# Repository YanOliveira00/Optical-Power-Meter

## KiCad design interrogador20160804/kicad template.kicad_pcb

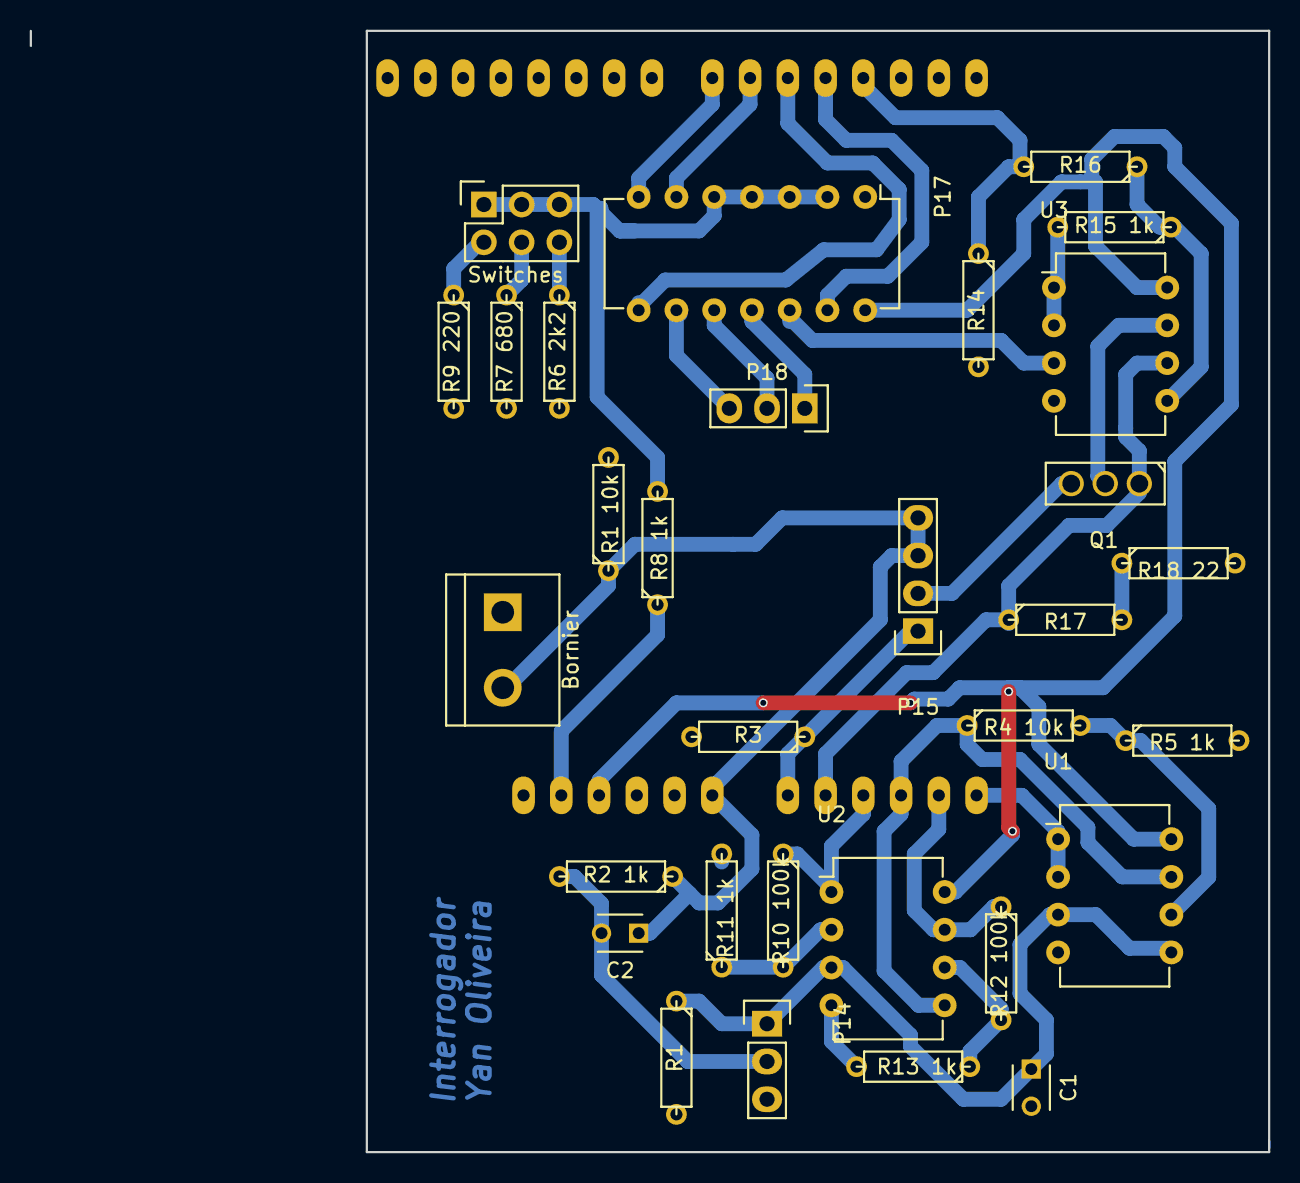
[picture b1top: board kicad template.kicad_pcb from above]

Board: 2 copper layers, 83.3 x 75.4 mm, 32 parts (1 on the bottom side), 33 nets.

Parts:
Bornier: PowerIn; bornier2
C1: 100p; C_Disc_D3_P2.5
C2: 100n; C_Disc_D3_P2.5
P14: Detector; Socket_Strip_Straight_1x03
P15: laser (PD+LD); Pin_Header_Straight_1x04
P17: TLC5620; DIP-14_W7.62mm
P18: extout; Socket_Strip_Straight_1x03
Q1: Q_NPN_EBC; SOT126_SOT32_Housing_Vertical
R1, R1 10k, R3, R4 10k: 10k; R3
R2 1k, R5 1k, R8 1k, R11 1k, R13 1k, R15 1k: 1k; R3
R6 2k2: 2k2; R3
R7 680: 680; R3
R9 220: 220; R3
R10 100k, R12 100k, R14: 100k; R3
R16: 15k; R3
R17: 10; R3
R18 22: 22; R3
SHIELD1: ARDUINO_SHIELD
Switches: CONN_02X03; Socket_Strip_Straight_2x03
U1, U2, U3: MCP6002; DIP-8_W7.62mm

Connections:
+3V3: R8 1k.1, SHIELD1.3V3
+5V: P17.14, SHIELD1.5V, U1.8, U2.8, U3.8
/1X: SHIELD1.AD5, U1.1, U1.2
/10X: R4 10k.1, SHIELD1.AD3, U1.7, U2.5
/100X: R10 100k.1, SHIELD1.AD2, U2.1
/1000X: R12 100k.1, SHIELD1.AD4, U2.7
/AMPFEED: Q1.1, R17.1, SHIELD1.AD1, U3.6
/CLK: P17.7, SHIELD1.7
/DAC_A: R15 1k.2, U3.1, U3.2
/DATA: P17.6, SHIELD1.6
/LD: P15.2, Q1.3
/LDAC: P17.13, SHIELD1.4
/LOAD: P17.8, SHIELD1.5
/MOD: R14.1, R16.2, SHIELD1.3
/PD: P15.1, R3.1, SHIELD1.AD0
/input: C1.1, P14.1, R1.1, U1.3, U1.5, U2.3
GND: Bornier.1, C1.2, P14.3, P17.1, R1.2, R1 10k.2, R3.2, R5 1k.2, R6 2k2.2, R7 680.2, R9 220.2, R11 1k.2, R13 1k.2, R14.2, R18 22.2, SHIELD1.GND1, SHIELD1.GND2, SHIELD1.GND3, U1.4, U2.4, U3.4
unnamed: C2.2, P14.2, R2 1k.2
unnamed: P17.2, P17.3, P17.4, P17.5, R8 1k.2, Switches.1, Switches.3, Switches.5
unnamed: R9 220.1, Switches.2
unnamed: R7 680.1, Switches.4
unnamed: R6 2k2.1, Switches.6
unnamed: P17.9, P18.3
unnamed: P17.10, P18.2
unnamed: P17.11, P18.1
unnamed: P17.12, U3.3
unnamed: Q1.2, U3.7
unnamed: R4 10k.2, R5 1k.1, U1.6
unnamed: R10 100k.2, R11 1k.1, U2.2
unnamed: R12 100k.2, R13 1k.1, U2.6
unnamed: R15 1k.1, R16.1, U3.5
unnamed: R17.2, R18 22.1
VCC: Bornier.2, C2.1, P15.3, P15.4, R1 10k.1, R2 1k.1, SHIELD1.V_IN

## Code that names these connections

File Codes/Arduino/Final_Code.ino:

//Código criado por Yan S. de Oliveira, em 2016.
//Código complementar feitos em Python.
//Corresponde ao TCC do curso de Engenharia da Computação UFPa.
//Editado e comentado em 17/03/2017 
//Definições iniciais
//Pinos do TLC5620 6,7,8 e 13, respectivamente.
#define PIN_DATA  6  
#define PIN_CLK   7  
#define PIN_LOAD  5  
#define PIN_LDAC  4  
#define PIN_MOD  3 //Trabalhos futuros 

//Portas que serão utilizadas para a placa e seus feedbacks
#define PIN_AMPFEED  A1
#define PIN_PDFEED A0
#define PIN_1X A5
#define PIN_100X A2
#define PIN_1000X A4
#define PIN_10X A3 

//Modos de escrita do TLC, vide datasheet.
#define DACA  0
#define DACB  1
#define DACC  2
#define DACD  3 

//Especificações para TLC, vide datasheet.
#define DAC_REF   0	// 1 * Vref
#define DAC_REFX2 1	// 2 * Vref
#define FREQUENCY 10 //Frequencia em uS 10 = 100kHz
float mapAMP = 0;//Valor de corrente real enviado pelo TLC
float corrente = 0;//Corrente lida do Serial
float VStep = 0; //Variação de tensão por step no TLC 
int limit = 0;//armazena o limitador recebido (1-3)
int steps = 0;//steps do TLC para envio de tensão ao ampop (0-255)
int Func =0;//Armazena função de leitura (1-6)

//variável abstrata para leitura dos pinos, após terem sido mapeados pela função map
float  leitura = 0; 
uint8_t TXT;

//union utilizado para converter um float em bytes e vice-versa
typedef union {
 short intPoint;
 byte binary[2];
} binaryInt; 
char ch;//Char que lerá o valor do limitador Ex.: '1'
char fim;//Recebe char que determina fim do ciclo solicitado pelo programa em Python 

void initTLC5620() {//inicia tlc
  pinMode(PIN_DATA, OUTPUT);
  pinMode(PIN_CLK,  OUTPUT);
  pinMode(PIN_LOAD, OUTPUT);
  pinMode(PIN_LDAC, OUTPUT); 
} //Ler limitadores, e identificar para os cálculos

void initLimit() {	//inicia limitador. Espera resposta. 
  while(limit<1 or limit>3) { //entre 1 e 3
	if (Serial.available()>0) { //Se houver byte no serial
      	ch=Serial.read();
      	limit = (int)ch - (int)'0'; //Inicia o limitador com o valor escolhido (1-3)   	
    	}  
  }
 }

//Ler Função
void initFunction() { //inicia limitador. Espera resposta.
  while(Func<1 or Func>6) { //entre 1 e 6
	if (Serial.available()>0) { //Se houver byte no serial
      	ch=Serial.read();
      	Func = (int)ch - (int)'0'; //Inicia o limitador com o valor escolhido (1-3)   	
    	}  
  }
  if(Func==1){
	TXT=PIN_AMPFEED;
  }
  if(Func==2){
	TXT=PIN_PDFEED;
  } 
  if(Func==3){
	TXT=PIN_1X;
  } 
  if(Func==4){
	TXT=PIN_10X;
  }  
  if(Func==5){
	TXT=PIN_100X;
  }
  if(Func==6){
	TXT=PIN_1000X;
  }
 }


 //escrita necessita de uma sincronia entre o Clock e a entrada
//de dados enviada por DATA. Com isso usamos a configuração MSB na subida do Clock
// e terminamos o dado usando o LSB no fim do pulso. Respeitando as instruções do datasheet do TLC5620
void writeTLC5620(int channel, int range, int data) { //formato padrão:
//writeTLC5620(DACA,DAC_REF,steps)
  int MSB;
  int LSB;
  MSB = (channel & 0x03) << 1 | (range & 0x01) << 0; //0000 0000(DACA) & 0000 0011 << 1 = 0000 0000 | 0000 0000(DAC_REF) & 0000 0001 = 0000 0000
  LSB = data;
  //datasheet tlc5620
  digitalWrite(PIN_LDAC, HIGH);
  digitalWrite(PIN_LOAD, HIGH);
  //organizando usando o shiftOut
  shiftOut(PIN_DATA, PIN_CLK, MSBFIRST, MSB);//highbyte
  shiftOut(PIN_DATA, PIN_CLK, MSBFIRST, LSB);//lowbyte 
  digitalWrite(PIN_LOAD, LOW);
  delayMicroseconds(FREQUENCY);//frequencia selecionada
  digitalWrite(PIN_LOAD, HIGH);
  delayMicroseconds(FREQUENCY);
  digitalWrite(PIN_LDAC, LOW);
  delayMicroseconds(FREQUENCY);
  digitalWrite(PIN_LDAC, HIGH);
  //pronto! Dado enviado para a porta escolhida
}

//Função para escrever_Serial
//Envia-se delimitadores de inicio e fim para então ser passado os 4 bytes do valor float, já calculado pelo Arduino
void send_int (short arg)
{ 
  binaryInt hi; //union hi criada.
  hi.intPoint = arg; //aponta para o valor que se quer enviar
  Serial.write('&');
  Serial.write(hi.binary,2);//envia o buffer com os bytes da union, representando o short "arg"
}

//mapear
  void mapear(int PIN) {
	leitura = analogRead(PIN);
	leitura *= (5.0 / 1023.0);
  } 

//PASSO 2:
//A função(def_current) irá receber o valor da corrente assinalada
//no Python e converter pra tensão necessária, considerando o
//limitador escolhido e o step necessário para fazer, de acordo com
//a corrente encontrada nos resistores.
//função def_steps recebe o float enviado pelo pyserial e transforma para steps viáveis ao TLC
void def_step(float i, float iMax) {
  if (i <= iMax) {
	steps = round((i * 255) / iMax);
  } else {
	steps = 255;
  }
} 
//determina corrente
void def_current() {
  corrente = -1.00;
  while (corrente <= 0) { //lê o char como float	
	if (Serial.available() > 0){
 	Serial.flush();//Espera o Serial para de enviar para então ler
  	corrente=Serial.parseFloat();	//Recebe uma sequencia e os transforma para float	
   }
  }
  //função que verifica limitadores
  limit=0;
  initLimit();
  Func=0;
  initFunction();  
  if (limit == 1) { //se limitador for 220 Ohm, sabemos que tensão máx é 0,595V. iMax=18.6 mA
	def_step(corrente, 18.25); //18.6 achado em calculo //calculará o número de steps que será escrito no TLC para atingir tal corrente
  }
  if (limit == 2) { //Corrente Máxima para esse limitador= 41.76mA
	def_step(corrente, 41.3); //41.76 achado em cálculo
  }
  if (limit == 3) { //Corrente Máxima para esse limitador = 70.9mA
	def_step(corrente, 70.45); //70.9 em cálculo
  } 
  //escrever no TLC com referencia setada em
  writeTLC5620(DACA, DAC_REF, steps);
 
}//fim função definir step 


//INÍCIO
void setup() {
  Serial.begin(250000);
  initTLC5620();//inicializa TLC
  writeTLC5620(DACA, DAC_REF, 0);//roda o vazio para evitar problemas de sobrecarga do laser
  def_current();//define os parametros de corrente. 
  pinMode(PIN_MOD, OUTPUT);  //inicializando MOD
  pinMode(PIN_PDFEED, INPUT);  //inicializando PDFEED
  pinMode(PIN_AMPFEED, INPUT);  //inicializando AMPFEED
  pinMode(PIN_1X, INPUT);  //inicializando 1X
  pinMode(PIN_10X, INPUT);  //inicializando 10X
  pinMode(PIN_100X, INPUT);  //inicializando 100X
  pinMode(PIN_1000X, INPUT);  //inicializando 1X 
}

//Considerando as funções que determinam passo 1 e 2, os passos seguintes se resumem a mostrar
//o que foi observado e armazenar em um file via pyserial.
void loop() {
  send_int(analogRead(TXT)); 
  //Ao fim da leitura, pySerial envia uma flag recomeçando o loop
  //logo, seta-se o TLC para 0 novamente e espera um novo valor de corrente e limitador
  if (Serial.available()>0){
	fim=Serial.read();
	if (fim=='9'){
    	writeTLC5620(DACA, DAC_REF, 0);
    	def_current();   	
  	}
	}
}

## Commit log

2018-02-28 Adicionando um readme para o código python.
2018-02-28 Adding readmes for python and arduino (C++) codes. All of it is in Pt-br.
2018-02-28 Adding photos, presentation and other stuffs.
